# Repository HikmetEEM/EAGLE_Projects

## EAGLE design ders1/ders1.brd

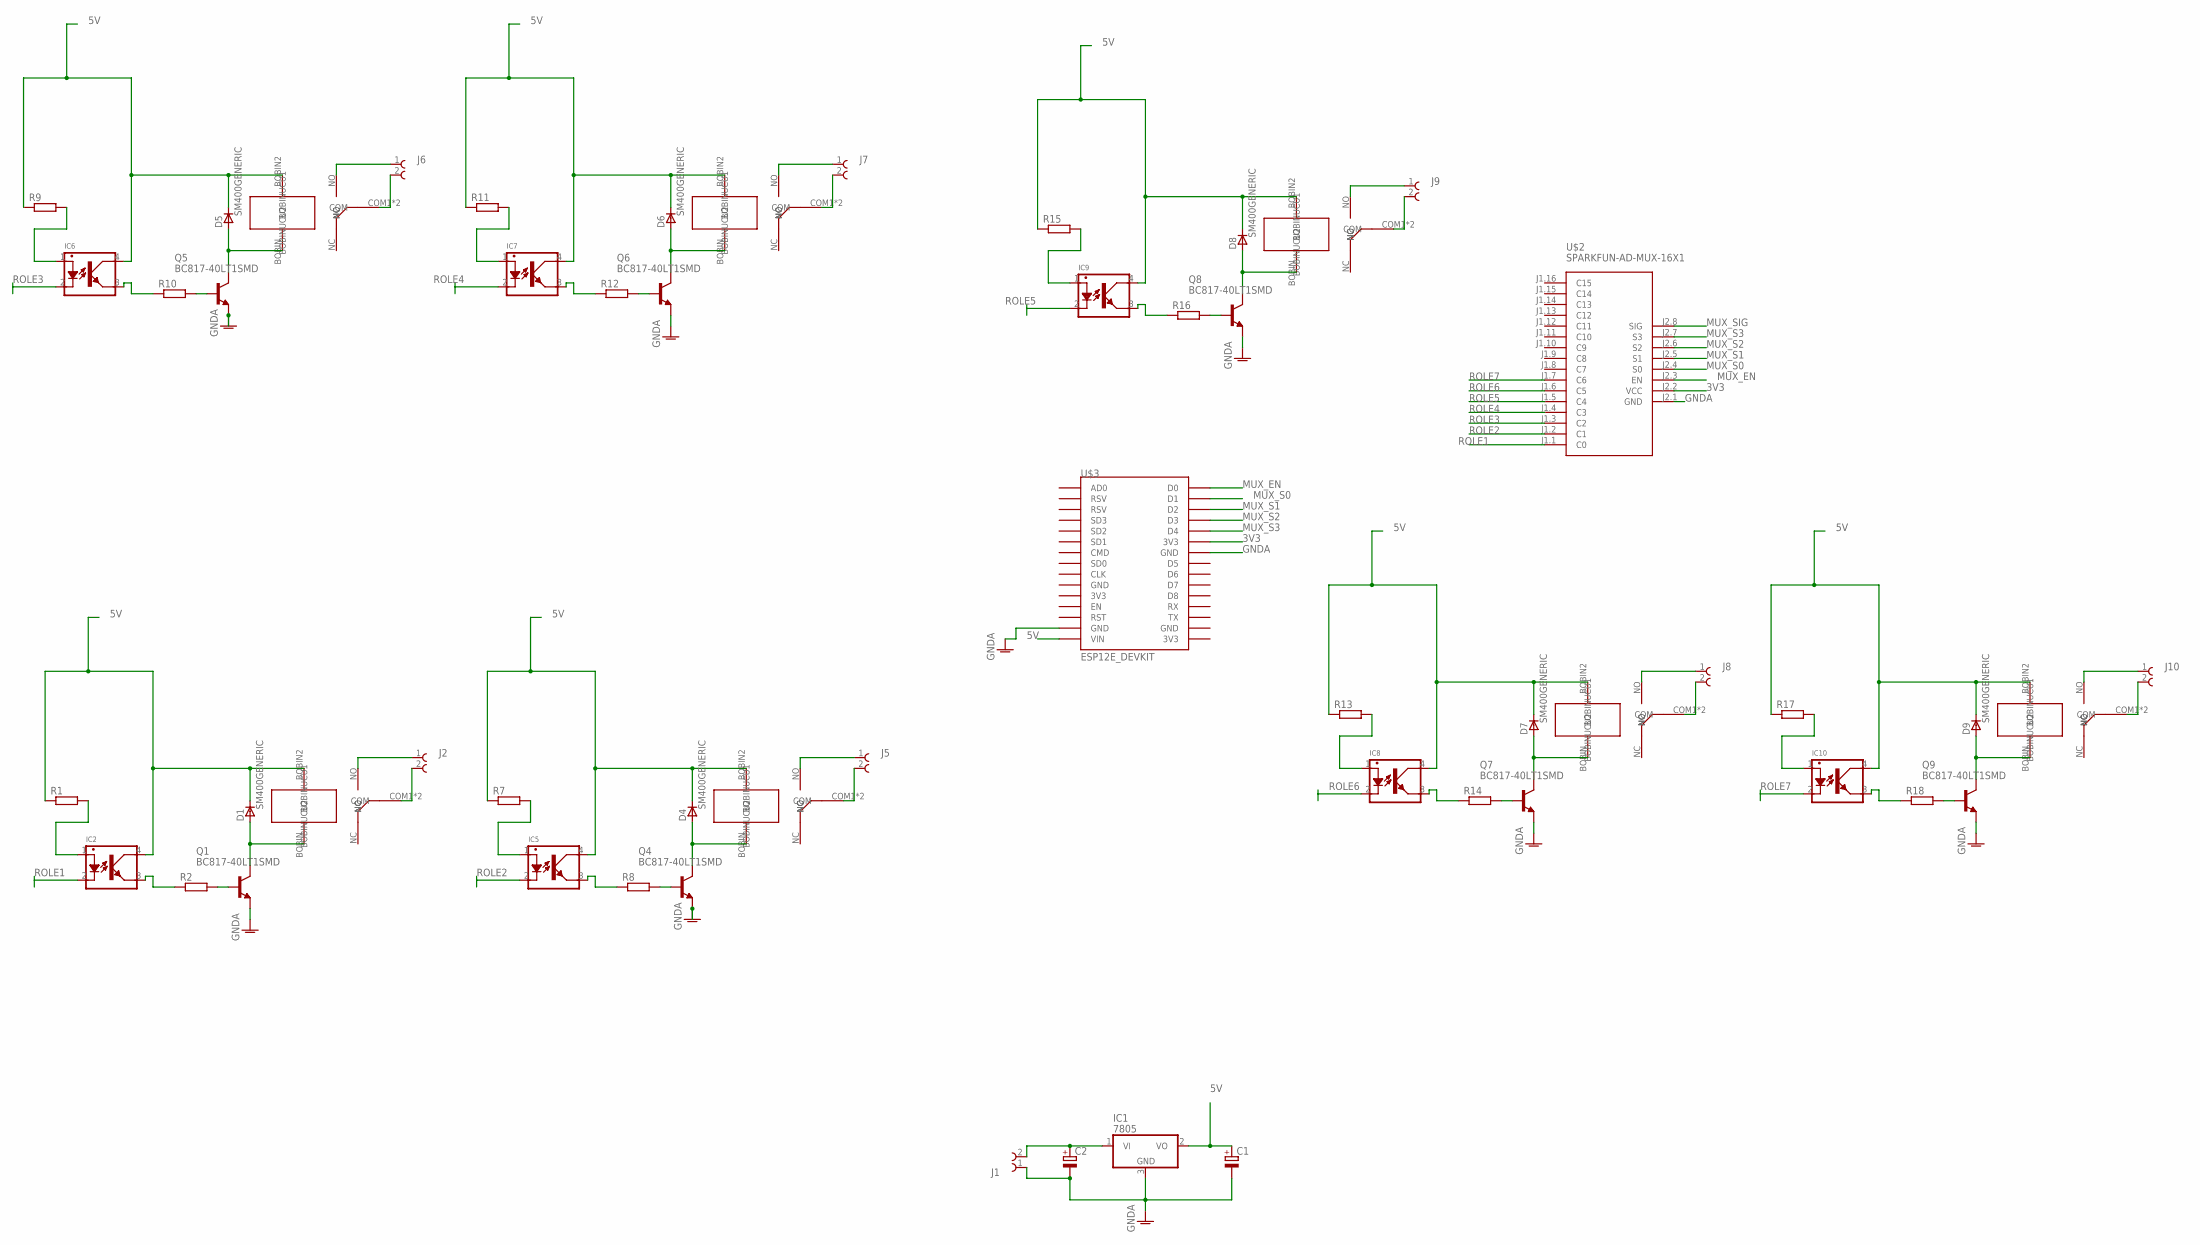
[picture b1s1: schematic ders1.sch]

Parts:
C1, C2: CPOL-EU153CLV-0405; 153CLV-0405
D1, D4, D5, D6, D7, D8, D9: SM400GENERIC; MELF-MLL41_DO213AB
IC1: 7805; TO252
IC2, IC5, IC6, IC7, IC8, IC9, IC10: LTV-817SMD; SMD-4
J1, J2, J5, J6, J7, J8, J9, J10: 691701540002B
Q1, Q4, Q5, Q6, Q7, Q8, Q9: BC817-40LT1SMD; SOT23-BEC
R1, R2, R7, R8, R9, R10, R11, R12, R13, R14, R15, R16, R17, R18: R-EU_R1206; R1206
U$1, U$4, U$5, U$6, U$7, U$8, U$9: HK23F-DC5V-SHG; HK23F
U$2: SPARKFUN-AD-MUX-16X1
U$3: ESP12E_DEVKIT

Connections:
3V3: U$2.J2.2 (VCC), U$3.3V3@1 (3V3)
5V: C1.+, D1.C, D4.C, D5.C, D6.C, D7.C, D8.C, D9.C, IC1.2 (VO), IC2.4, IC5.4, IC6.4, IC7.4, IC8.4, IC9.4, IC10.4, R1.1, R7.1, R9.1, R11.1, R13.1, R15.1, R17.1, U$1.BOBIN2 (BOBINUCU2), U$3.VIN, U$4.BOBIN2 (BOBINUCU2), U$5.BOBIN2 (BOBINUCU2), U$6.BOBIN2 (BOBINUCU2), U$7.BOBIN2 (BOBINUCU2), U$8.BOBIN2 (BOBINUCU2), U$9.BOBIN2 (BOBINUCU2)
GNDA: C1.-, C2.-, IC1.3 (GND), J1.1, Q1.E, Q4.E, Q5.E, Q6.E, Q7.E, Q8.E, Q9.E, U$2.J2.1 (GND), U$3.GND@1 (GND), U$3.GND@2 (GND)
MUX_EN: U$2.J2.3 (EN), U$3.D0
MUX_S0: U$2.J2.4 (S0), U$3.D1
MUX_S1: U$2.J2.5 (S1), U$3.D2
MUX_S2: U$2.J2.6 (S2), U$3.D3
MUX_S3: U$2.J2.7 (S3), U$3.D4
MUX_SIG: U$2.J2.8 (SIG)
unnamed: C2.+, IC1.1 (VI), J1.2
unnamed: D1.A, Q1.C, U$1.BOBIN (BOBINUCU1)
unnamed: Q1.B, R2.2
unnamed: IC2.3, R2.1
unnamed: IC2.1, R1.2
unnamed: J2.2, U$1.COM1 (COM), U$1.COM2 (COM)
unnamed: J2.1, U$1.NO
unnamed: D4.A, Q4.C, U$4.BOBIN (BOBINUCU1)
unnamed: Q4.B, R8.2
unnamed: IC5.3, R8.1
unnamed: IC5.1, R7.2
unnamed: J5.2, U$4.COM1 (COM), U$4.COM2 (COM)
unnamed: J5.1, U$4.NO
unnamed: D5.A, Q5.C, U$5.BOBIN (BOBINUCU1)
unnamed: Q5.B, R10.2
unnamed: IC6.3, R10.1
unnamed: IC6.1, R9.2
unnamed: J6.2, U$5.COM1 (COM), U$5.COM2 (COM)
unnamed: J6.1, U$5.NO
unnamed: D6.A, Q6.C, U$6.BOBIN (BOBINUCU1)
unnamed: Q6.B, R12.2
unnamed: IC7.3, R12.1
unnamed: IC7.1, R11.2
unnamed: J7.2, U$6.COM1 (COM), U$6.COM2 (COM)
unnamed: J7.1, U$6.NO
unnamed: D7.A, Q7.C, U$7.BOBIN (BOBINUCU1)
unnamed: Q7.B, R14.2
unnamed: IC8.3, R14.1
unnamed: IC8.1, R13.2
unnamed: J8.2, U$7.COM1 (COM), U$7.COM2 (COM)
unnamed: J8.1, U$7.NO
unnamed: D8.A, Q8.C, U$8.BOBIN (BOBINUCU1)
unnamed: Q8.B, R16.2
unnamed: IC9.3, R16.1
unnamed: IC9.1, R15.2
unnamed: J9.2, U$8.COM1 (COM), U$8.COM2 (COM)
unnamed: J9.1, U$8.NO
unnamed: D9.A, Q9.C, U$9.BOBIN (BOBINUCU1)
unnamed: Q9.B, R18.2
unnamed: IC10.3, R18.1
unnamed: IC10.1, R17.2
unnamed: J10.2, U$9.COM1 (COM), U$9.COM2 (COM)
unnamed: J10.1, U$9.NO
ROLE1: IC2.2, U$2.J1.1 (C0)
ROLE2: IC5.2, U$2.J1.2 (C1)
ROLE3: IC6.2, U$2.J1.3 (C2)
ROLE4: IC7.2, U$2.J1.4 (C3)
ROLE5: IC9.2, U$2.J1.5 (C4)
ROLE6: IC8.2, U$2.J1.6 (C5)
ROLE7: IC10.2, U$2.J1.7 (C6)

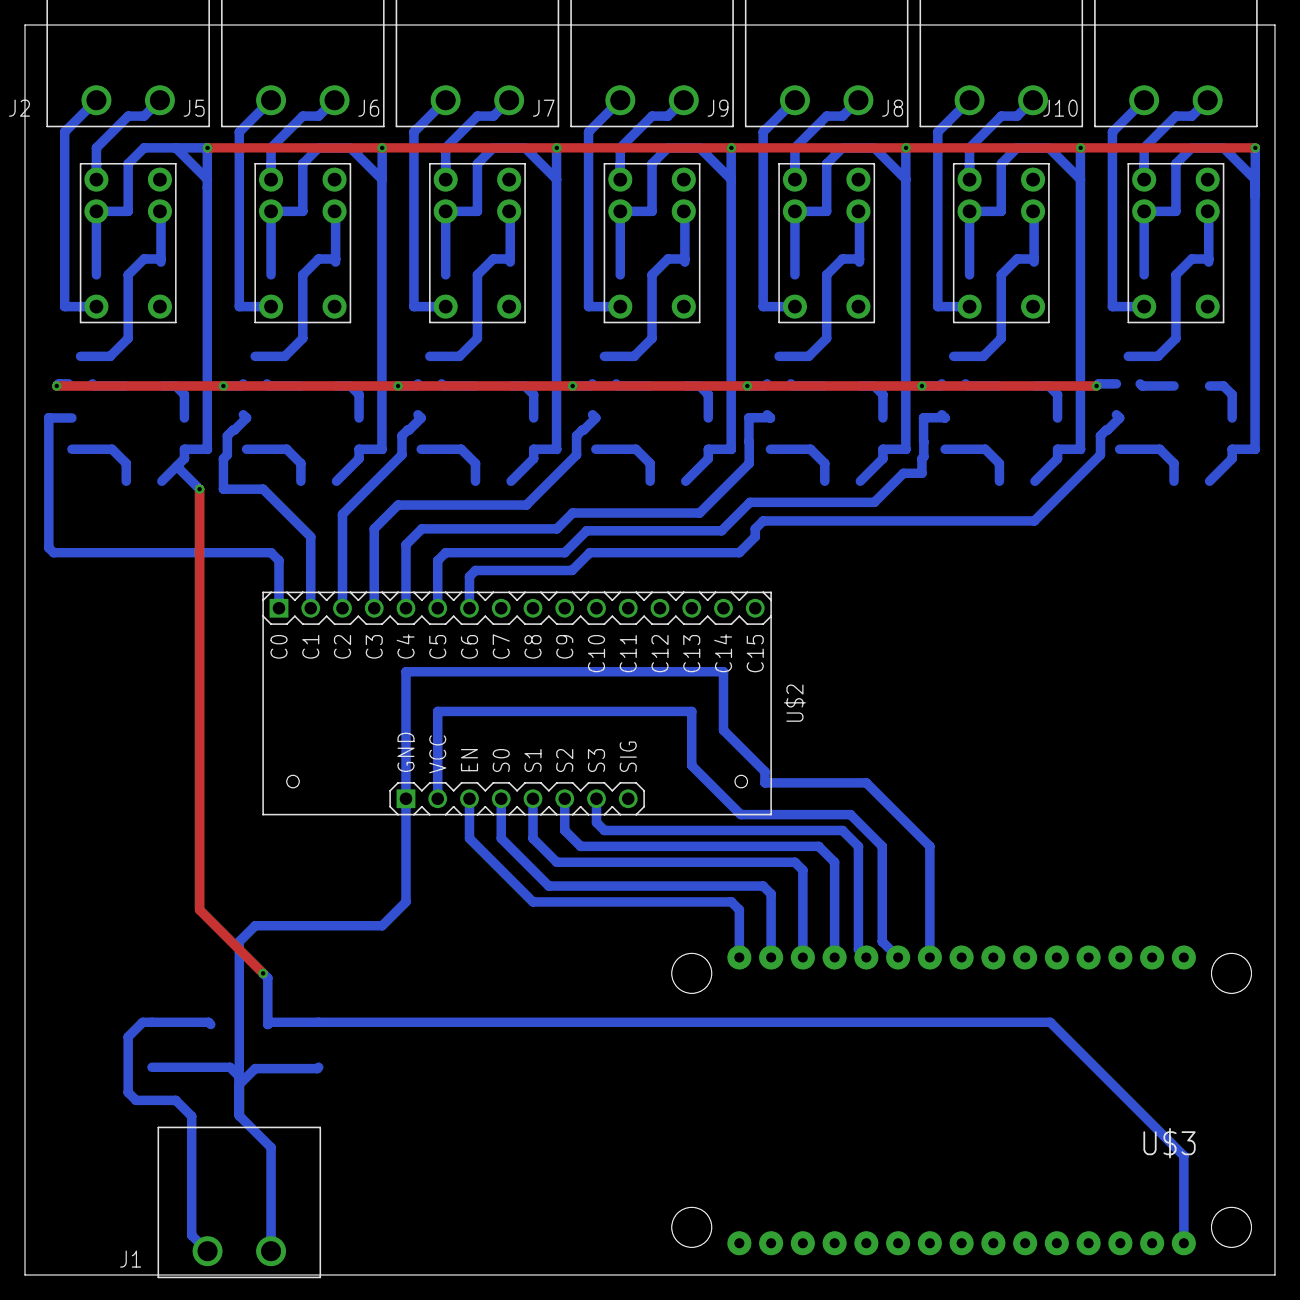
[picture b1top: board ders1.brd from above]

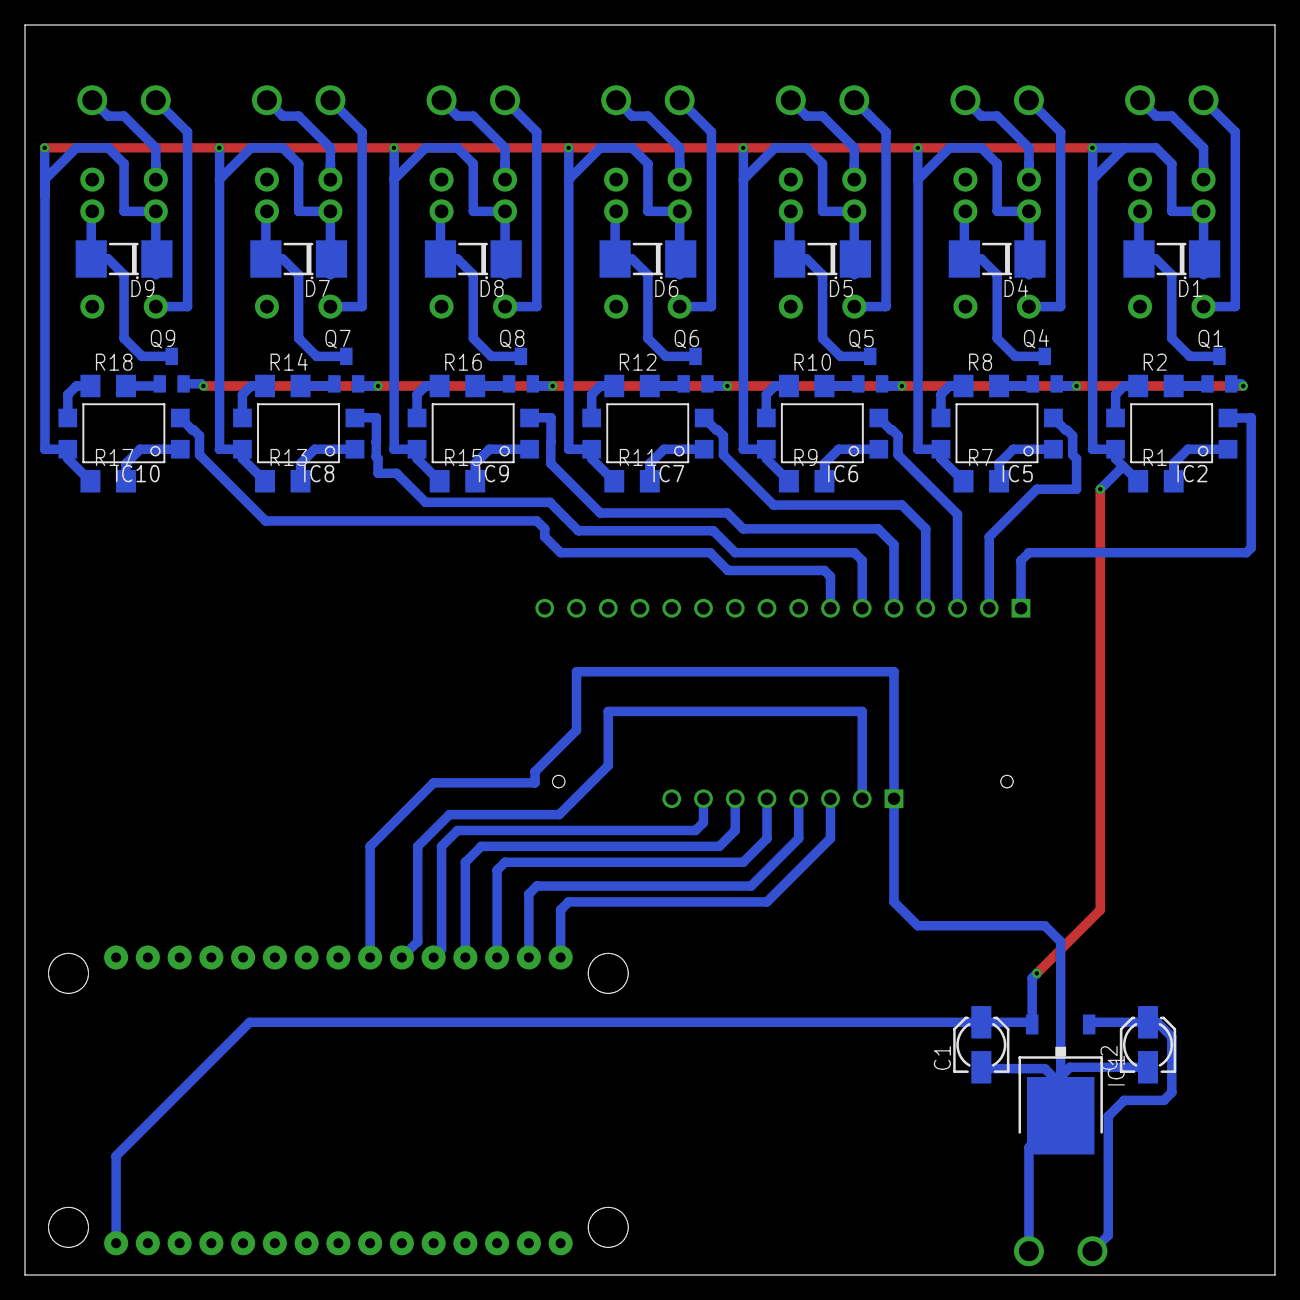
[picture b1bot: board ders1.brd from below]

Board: 2 copper layers, 100.0 x 100.0 mm, 55 parts (38 on the bottom side), 58 nets.

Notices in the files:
parts and their libraries:
Wurth_Elektronik_Electromechanic_Termina: Copyright: Würth Elektronik
diy-modules: Released under the Creative Commons Attribution 4.0 International License: http://creativecommons.org/licenses/by/4.0
